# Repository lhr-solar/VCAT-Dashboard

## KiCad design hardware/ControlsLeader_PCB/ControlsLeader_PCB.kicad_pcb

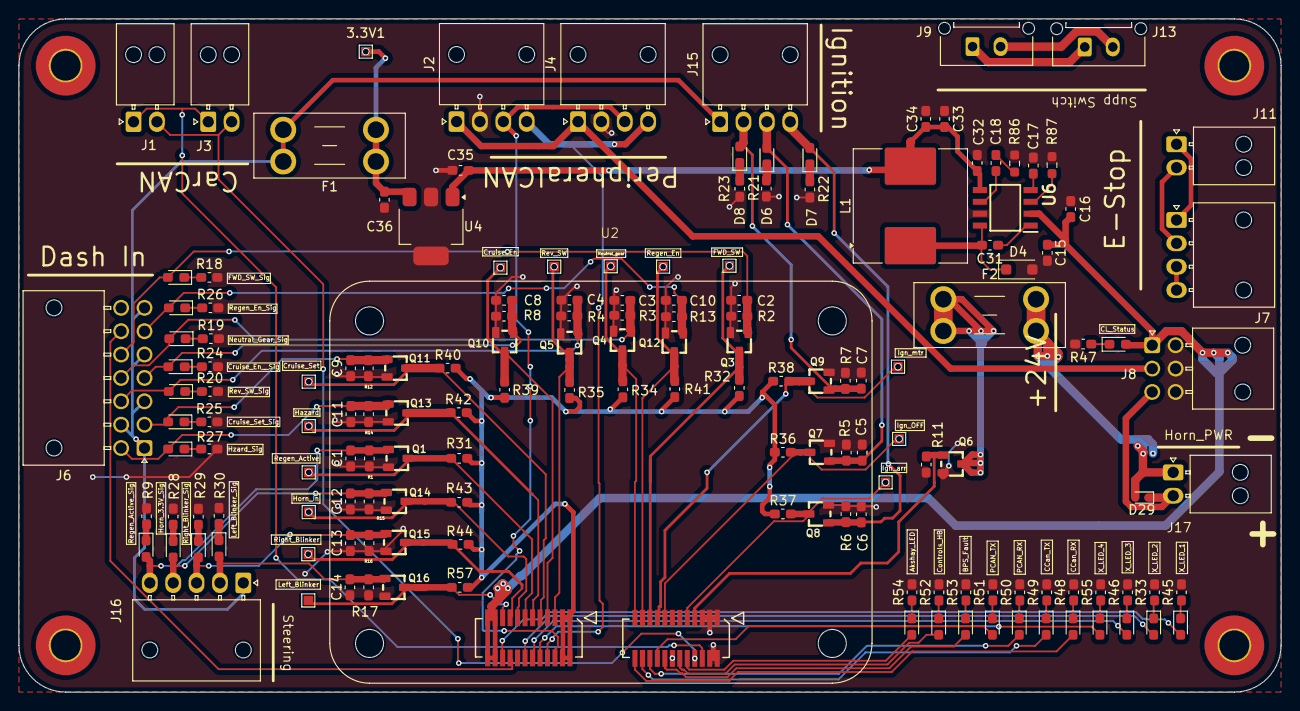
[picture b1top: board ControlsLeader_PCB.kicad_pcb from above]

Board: 2 copper layers, 135.0 x 72.0 mm, 162 parts (0 on the bottom side), 92 nets.

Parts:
3.3V1: TestPoint; TestPoint_Pad_1.0x1.0mm
C1, C2, C3, C4, C5, C6, C7, C8, C9, C10, C11, C12, C13, C14: 5uF; C_0603_1608Metric_Pad1.08x0.95mm_HandSolder
C15, C32, C33, C34, C35, C36: 10uF; C_0603_1608Metric_Pad1.08x0.95mm_HandSolder
C16: 1uF; C_0603_1608Metric_Pad1.08x0.95mm_HandSolder
C17: 10nF; C_0603_1608Metric_Pad1.08x0.95mm_HandSolder
C18: 3.3nF; C_0603_1608Metric_Pad1.08x0.95mm_HandSolder
C31: 0.1uF; C_0603_1608Metric_Pad1.08x0.95mm_HandSolder
Cruise_En: TestPoint; TestPoint_Pad_1.0x1.0mm
Cruise_En__Sig: GPIO_Status_Blue; LED_0603_1608Metric_Pad1.05x0.95mm_HandSolder
Cruise_Set: TestPoint; TestPoint_Pad_1.0x1.0mm
Cruise_Set_Sig: GPIO_Status_Blue; LED_0603_1608Metric_Pad1.05x0.95mm_HandSolder
D4: MBR230S1F; D_SOD-123F
D6, D7, D8: GPIO_Status_Blue; LED_0603_1608Metric_Pad1.05x0.95mm_HandSolder
D16: Controls_Leader_Status_Red; LED_0603_1608Metric_Pad1.05x0.95mm_HandSolder
D17, D18, D19, D20, D21, D22, D23, D24, D25, D26, D27: 0603_SMD; LED_0603_1608Metric_Pad1.05x0.95mm_HandSolder
D29: VSSAF522-M3/H; D_SOD-523
F1, F2: Fuse; Fuseholder_Blade_Mini_Keystone_3568
FWD_SW: TestPoint; TestPoint_Pad_1.0x1.0mm
FWD_SW_Sig: GPIO_Status_Blue; LED_0603_1608Metric_Pad1.05x0.95mm_HandSolder
H1, H2, H3, H4: M.3; MountingHole_3.2mm_M3_Pad_TopBottom
Hazard: TestPoint; TestPoint_Pad_1.0x1.0mm
Horn_3.3V_Sig: GPIO_Status_Blue; LED_0603_1608Metric_Pad1.05x0.95mm_HandSolder
Horn_In: TestPoint; TestPoint_Pad_1.0x1.0mm
Hzard_Sig: GPIO_Status_Blue; LED_0603_1608Metric_Pad1.05x0.95mm_HandSolder
Ign_OFF: TestPoint; TestPoint_Pad_1.0x1.0mm
Ign_arr: TestPoint; TestPoint_Pad_1.0x1.0mm
Ign_mtr: TestPoint; TestPoint_Pad_1.0x1.0mm
J1: CarCANConnector_Out; Molex_Nano-Fit_105313-xx02_1x02_P2.50mm_Horizontal
J2: PeripheralCAN_out; Molex_Nano-Fit_105313-xx04_1x04_P2.50mm_Horizontal
J3: CarCANConnector_In; Molex_Nano-Fit_105313-xx02_1x02_P2.50mm_Horizontal
J4: PeripheralCAN_in; Molex_Nano-Fit_105313-xx04_1x04_P2.50mm_Horizontal
J6: Conn_2Rows-13Pins; Molex_Nano-Fit_105314-xx14_2x07_P2.50mm_Horizontal
J7: Conn_01x04; Molex_Nano-Fit_105313-xx04_1x04_P2.50mm_Horizontal
J8: Dash_Lsom_Horn_Lights_PWR; Molex_Nano-Fit_105314-xx06_2x03_P2.50mm_Horizontal
J9: Supp_In; Molex_Micro-Fit_3.0_43650-0215_1x02_P3.00mm_Vertical
J11: EStop1; Molex_Nano-Fit_105313-xx02_1x02_P2.50mm_Horizontal
J13: Supp_Out; Molex_Micro-Fit_3.0_43650-0215_1x02_P3.00mm_Vertical
J15: IgnConn_01x04; Molex_Nano-Fit_105313-xx04_1x04_P2.50mm_Horizontal
J16: SteeringConn_01x05; Molex_Nano-Fit_105313-xx05_1x05_P2.50mm_Horizontal
J17: Conn_01x02; Molex_Nano-Fit_105313-xx02_1x02_P2.50mm_Horizontal
L1: 100uH; L_Coilcraft_MSS1246-XXX
Left_Blinker: TestPoint; TestPoint_Pad_1.0x1.0mm
Left_Blinker_Sig: GPIO_Status_Blue; LED_0603_1608Metric_Pad1.05x0.95mm_HandSolder
Neutral_Gear_Sig: GPIO_Status_Blue; LED_0603_1608Metric_Pad1.05x0.95mm_HandSolder
Neutral_gear: TestPoint; TestPoint_Pad_1.0x1.0mm
Q1, Q3, Q4, Q5, Q6, Q7, Q8, Q9, Q10, Q11, Q12, Q13, Q14, Q15, Q16: NMOS; SOT23
R1, R2, R3, R4, R5, R6, R7, R8, R11, R12, R13, R14, R15, R16, R17: 10k; C_0603_1608Metric_Pad1.08x0.95mm_HandSolder
R9, R18, R19, R20, R21, R22, R23, R24, R25, R26, R27, R28, R29, R30: 150; C_0603_1608Metric_Pad1.08x0.95mm_HandSolder
R31, R32, R34, R35, R36, R37, R38, R39, R40, R41, R42, R43, R44, R57: 100k; C_0603_1608Metric_Pad1.08x0.95mm_HandSolder
R33, R45, R46, R55: 65; C_0603_1608Metric_Pad1.08x0.95mm_HandSolder
R47: 1.1k; C_0603_1608Metric_Pad1.08x0.95mm_HandSolder
R48, R49, R50, R51, R52, R53, R54: 20; C_0603_1608Metric_Pad1.08x0.95mm_HandSolder
R86: 16k; R_0603_1608Metric_Pad0.98x0.95mm_HandSolder
R87: ROSC; R_0603_1608Metric_Pad0.98x0.95mm_HandSolder
Regen_Active: TestPoint; TestPoint_Pad_1.0x1.0mm
Regen_Active_Sig: GPIO_Status_Blue; LED_0603_1608Metric_Pad1.05x0.95mm_HandSolder
Regen_En: TestPoint; TestPoint_Pad_1.0x1.0mm
Regen_En_Sig: GPIO_Status_Blue; LED_0603_1608Metric_Pad1.05x0.95mm_HandSolder
Rev_SW: TestPoint; TestPoint_Pad_1.0x1.0mm
Rev_SW_Sig: GPIO_Status_Blue; LED_0603_1608Metric_Pad1.05x0.95mm_HandSolder
Right_Blinker: TestPoint; TestPoint_Pad_1.0x1.0mm
Right_Blinker_Sig: GPIO_Status_Blue; LED_0603_1608Metric_Pad1.05x0.95mm_HandSolder
U2: LeaderSOM
U4: LT1963AEST-3.3#TRPBF; SOT-223-3_TabPin2
U6: TPS5405DR

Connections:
+24V: C15.1, C16.1, D16.2 (A), J8.1, U2.21 (24VExt), U2.22 (24VExt), U2.23 (24VExt), U2.24 (24VExt), U6.2 (VIN)
/3.3V_LDO: F1.2, J6.1, J6.3, J6.5, J6.7, J6.9, J15.1, J16.1
/3.3V_LSOM: R31.1, R32.1, R34.1, R35.1, R36.1, R37.1, R38.1, R39.1, R40.1, R41.1, R42.1, R43.1, R44.1, R57.1, U2.1 (+3.3V), U2.2 (+3.3V), U2.3 (+3.3V), U2.4 (+3.3V)
/5V_LDO: C32.1, C33.1, C34.1, C35.1, L1.2, U4.1 (IN), U6.5 (VSENSE)
/5v_3.3v_LDO/3.3V_LDO: 3.3V1.1, C36.1, F1.1, U4.3 (OUT)
/24v_5v_Buck/ROSC: R87.1, U6.3 (ROSC)
/+24v_Horn: D29.1 (K), J8.3, J17.2
/+24v_Lights: J2.1 (24V), J4.1 (24V), J8.2
/Akshay_LED: D25.2 (A), U2.34 (UART4_TX)
/BPS_Fault_LED: D24.2 (A), U2.40 (ADC1_IN7)
/CarCan_H: J1.1 (CAN_H), J3.1 (CAN_H), U2.30 (CarCAN_H)
/CarCan_L: J1.2 (CAN_L), J3.2 (CAN_L), U2.32 (CarCAN_L)
/CarCan_RX_LED: D19.2 (A), U2.48 (SPI3_SCK)
/CarCan_TX_LED: D20.2 (A), U2.46 (SPI3_MOSI)
/Controls_HB_LED: D23.2 (A), U2.36 (UART4_RX)
/Cruise_Enable_GPIO_IN: Cruise_En.1, Q10.1 (D), R39.2, U2.7 (I2C4_SCL)
/Cruise_Enable_Signal: C8.2, Cruise_En__Sig.2 (A), J6.4, Q10.2 (G), R8.2
/Cruise_Set_GPIO_IN: Cruise_Set.1, Q11.1 (D), R40.2, U2.9 (I2C3_SDA)
/Cruise_Set_Signal: C9.2, Cruise_Set_Sig.2 (A), J6.2, Q11.2 (G), R12.2
/Dash/Contactor_IN1: J7.2, J11.2
/Dash/Contactor_OUT1: J7.1, J11.1
/Dash/Contactor_OUT2: J7.3, J7.4
/Dash/LV-: J9.2, J13.2
/Dash/LV_EN: J9.1, J13.1
/Extra_LED1: D17.2 (A), U2.20 (SPI2_SCK)
/Extra_LED2: D18.2 (A), U2.14 (SPI2_MISO)
/Extra_LED3: D26.2 (A), U2.12 (ADC1_IN11)
/Extra_LED4: D27.2 (A), U2.10 (ADC2_IN12)
/Fwd_SW_GPIO: FWD_SW.1, Q3.1 (D), R32.2, U2.43 (ADC1_IN1)
/Fwd_SW_Signal: C2.2, FWD_SW_Sig.2 (A), J6.12, Q3.2 (G), R2.2
/Hazard_GPIO_IN: Hazard.1, Q13.1 (D), R42.2, U2.11 (I2C3_SCL)
/Hazard_Signal: C11.2, Hzard_Sig.2 (A), J6.8, Q13.2 (G), R14.2
/Horn_3.3V_Signal: C12.2, Horn_3.3V_Sig.2 (A), J16.4, Q14.2 (G), R15.2
/Horn_24V_Signal_Out: D29.2 (A), F2.2, J17.1
/Horn_GPIO_IN: Horn_In.1, Q14.1 (D), R43.2, U2.15 (UART5_RX)
/Horn_GPIO_OUT: Q6.2 (G), R11.1, U2.31 (ADC1_IN12)
/Ign_OFF_GPIO: Ign_OFF.1, Q7.1 (D), R36.2, U2.39 (ADC1_IN3)
/Ign_arr_GPIO: Ign_arr.1, Q8.1 (D), R37.2, U2.33 (ADC1_IN15)
/Ign_arr_Signal: C6.2, D7.2 (A), J15.4, Q8.2 (G), R6.2
/Ign_mtr_GPIO: Ign_mtr.1, Q9.1 (D), R38.2, U2.41 (ADC1_IN2)
/Ign_mtr_Signal: C7.2, D8.2 (A), J15.2, Q9.2 (G), R7.2
/Ign_off_Signal: C5.2, D6.2 (A), J15.3, Q7.2 (G), R5.2
/Indicator_PWM: J6.13, U2.18 (SPI2_MOSI)
/Left_Blinker_ON: Left_Blinker.1, Q16.1 (D), R57.2, U2.19 (USART1_RX)
/Left_Blinker_Signal: C14.2, J16.2, Left_Blinker_Sig.2 (A), Q16.2 (G), R17.2
/Neutral_Gear_GPIO: Neutral_gear.1, Q4.1 (D), R34.2, U2.47 (ADC1_IN6)
/Neutral_Gear_Signal: C3.2, J6.11, Neutral_Gear_Sig.2 (A), Q4.2 (G), R3.2
/PH_Can_RX_LED: D21.2 (A), U2.44 (SPI3_NSS)
/PH_Can_TX_LED: D22.2 (A), U2.42 (SPI3_MISO)
/PerCan_H: J2.3 (CAN_H), J4.3 (CAN_H), U2.6 (IntCAN_H)
/PerCan_L: J2.4 (CAN_L), J4.4 (CAN_L), U2.8 (IntCAN_L)
/Regen_Active_GPIO_IN: Q1.1 (D), R31.2, Regen_Active.1, U2.13 (UART5_TX)
/Regen_Active_Signal: C1.2, J16.5, Q1.2 (G), R1.2, Regen_Active_Sig.2 (A)
/Regen_Enable_GPIO_IN: Q12.1 (D), R41.2, Regen_En.1, U2.45 (ADC1_IN8)
/Regen_Enable_Signal: C10.2, J6.6, Q12.2 (G), R13.2, Regen_En_Sig.2 (A)
/Rev_SW_GPIO: Q5.1 (D), R35.2, Rev_SW.1, U2.5 (I2C4_SDA)
/Rev_SW_Signal: C4.2, J6.10, Q5.2 (G), R4.2, Rev_SW_Sig.2 (A)
/Right_Blinker_ON: Q15.1 (D), R44.2, Right_Blinker.1, U2.17 (USART1_TX)
/Right_Blinker_Signal: C13.2, J16.3, Q15.2 (G), R16.2, Right_Blinker_Sig.2 (A)
GND: C1.1, C2.1, C3.1, C4.1, C5.1, C6.1, C7.1, C8.1, C9.1, C10.1, C11.1, C12.1, C13.1, C14.1, C15.2, C16.2, C17.2, C32.2, C33.2, C34.2, C35.2, C36.2, D4.2 (A), J2.2 (GND), J4.2 (GND), J8.4, J8.5, J8.6, Q1.3 (S), Q3.3 (S), Q4.3 (S), Q5.3 (S), Q6.3 (S), Q7.3 (S), Q8.3 (S), Q9.3 (S), Q10.3 (S), Q11.3 (S), Q12.3 (S), Q13.3 (S), Q14.3 (S), Q15.3 (S), Q16.3 (S), R1.1, R2.1, R3.1, R4.1, R5.1, R6.1, R7.1, R8.1, R9.2, R11.2, R12.1, R13.1, R14.1, R15.1, R16.1, R17.1, R18.2, R19.2, R20.2, R21.2, R22.2, R23.2, R24.2, R25.2, R26.2, R27.2, R28.2, R29.2, R30.2, R33.2, R45.2, R46.2, R47.2, R48.2, R49.2, R50.2, R51.2, R52.2, R53.2, R54.2, R55.2, R86.2, R87.2, U2.25 (GND), U2.26 (GND), U2.27 (GND), U2.28 (GND), U2.29 (GND), U2.38 (GNDA), U4.2 (GND), U6.7 (GND)
unnamed: C18.2, R86.1
unnamed: R9.1, Regen_Active_Sig.1 (K)
unnamed: FWD_SW_Sig.1 (K), R18.1
unnamed: Neutral_Gear_Sig.1 (K), R19.1
unnamed: C31.2, D4.1 (K), L1.1, U6.8 (LX)
unnamed: R20.1, Rev_SW_Sig.1 (K)
unnamed: D6.1 (K), R21.1
unnamed: D7.1 (K), R22.1
unnamed: D8.1 (K), R23.1
unnamed: Cruise_En__Sig.1 (K), R24.1
unnamed: Cruise_Set_Sig.1 (K), R25.1
unnamed: R26.1, Regen_En_Sig.1 (K)
unnamed: Hzard_Sig.1 (K), R27.1
unnamed: Horn_3.3V_Sig.1 (K), R28.1
unnamed: R29.1, Right_Blinker_Sig.1 (K)
unnamed: Left_Blinker_Sig.1 (K), R30.1
unnamed: D16.1 (K), R47.1
unnamed: D17.1 (K), R45.1
unnamed: D18.1 (K), R33.1
unnamed: D19.1 (K), R48.1
unnamed: D20.1 (K), R49.1
unnamed: D21.1 (K), R50.1
unnamed: D22.1 (K), R51.1
unnamed: D23.1 (K), R52.1
unnamed: D24.1 (K), R53.1
unnamed: D25.1 (K), R54.1
unnamed: D26.1 (K), R46.1
unnamed: D27.1 (K), R55.1
unnamed: F2.1, Q6.1 (D)
unnamed: C31.1, U6.1 (BOOT)
unnamed: C18.1, U6.6 (COMP)
unnamed: C17.1, U6.4 (SS)

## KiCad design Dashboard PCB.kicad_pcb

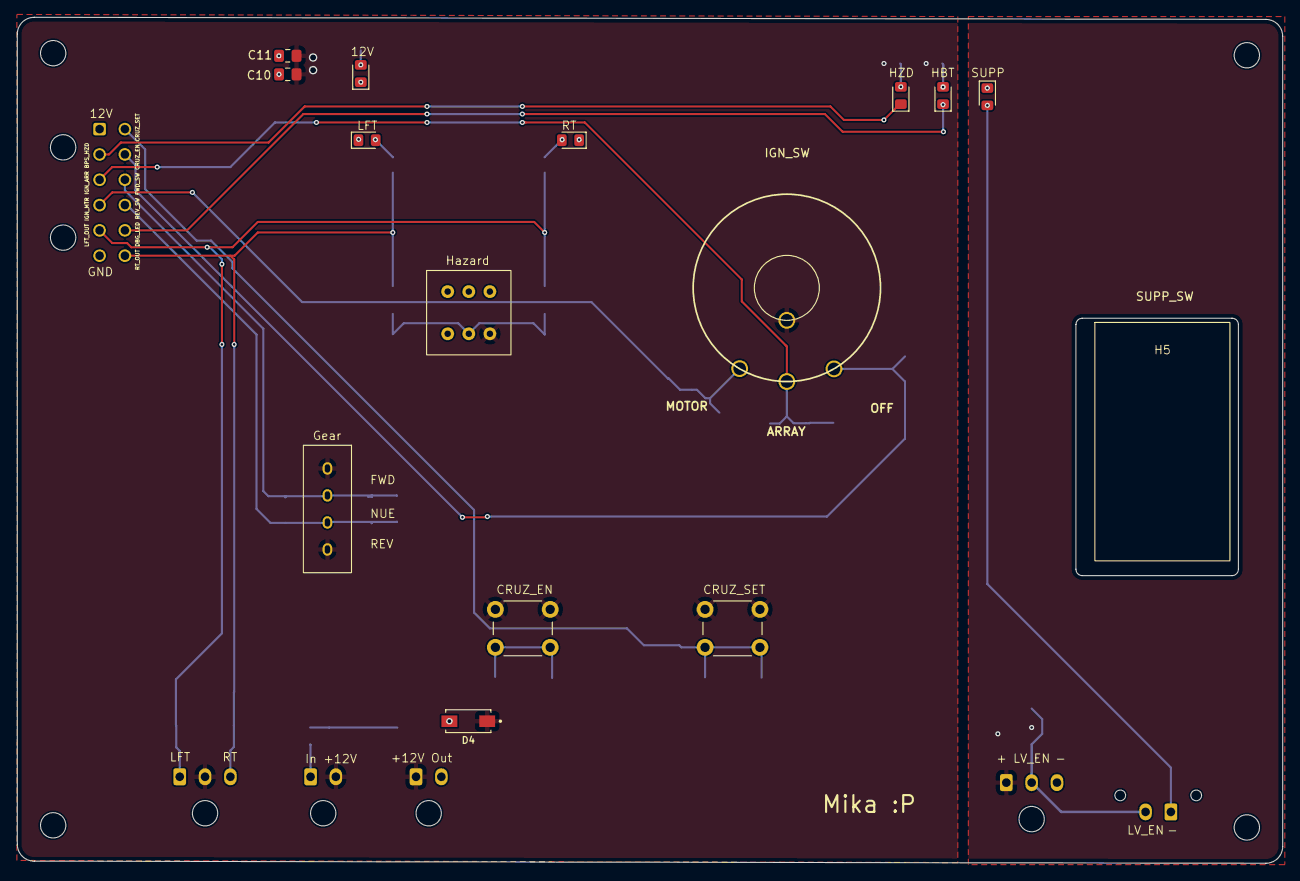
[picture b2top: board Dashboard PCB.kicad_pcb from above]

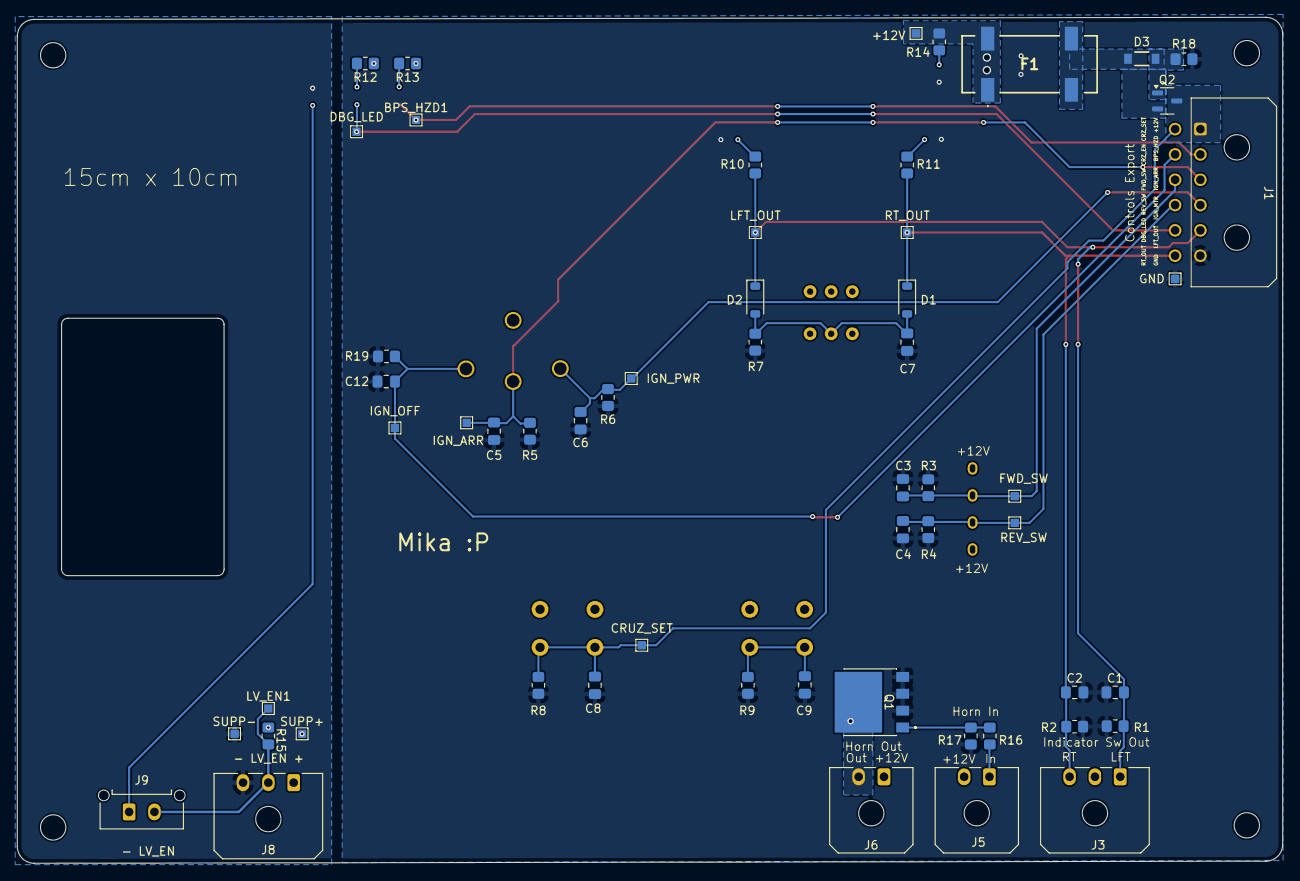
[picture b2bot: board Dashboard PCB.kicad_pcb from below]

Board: 2 copper layers, 150.0 x 100.2 mm, 75 parts (56 on the bottom side), 28 nets.

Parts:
12V_PWR1: SMD_0805; LED_0805_2012Metric_Pad1.15x1.40mm_HandSolder
+12V: TestPoint; TestPoint_Pad_1.0x1.0mm
BPS_HZD1: TestPoint; TestPoint_Pad_1.0x1.0mm
BPS_HZD_LED1: SMD_0805_RED; LED_0805_2012Metric_Pad1.15x1.40mm_HandSolder
C1, C2, C3, C4, C5, C6, C7, C8, C9, C12: 5uF; C_0805_2012Metric_Pad1.18x1.45mm_HandSolder
C10, C11: 100uF; C_0805_2012Metric_Pad1.18x1.45mm_HandSolder
CRUZ_EN_SW1: CRUSE_EN_SW_12V; SW_PUSH_6mm
CRUZ_SET: TestPoint; TestPoint_Pad_1.0x1.0mm
CRUZ_SET_SW1: CRUSE_SET_SW_12V; SW_PUSH_6mm
D1, D2: BAV16W; D_SOD-123
D3: BZT52-B12-QX; BZT52B12QX
D4: VSSAF522; DO-221AC
DBG_LED: TestPoint; TestPoint_Pad_1.0x1.0mm
F1: Fuse; 3588
FWD_SW: TestPoint; TestPoint_Pad_1.0x1.0mm
GEAR_SW_12V1: GR_SW1; 3posSlideToggle
GND: TestPoint; TestPoint_Pad_1.0x1.0mm
H1, H2, H3, H4: MountingHole; MountingHole_3mm
H5: SuppSwitchMount; Supp_Switch
HZD_SW1: HAZARD_SWITCH_12V; Toggle
Heartbeat_LED1: SMD_0805_GRN; LED_0805_2012Metric_Pad1.15x1.40mm_HandSolder
IGN_ARR: TestPoint; TestPoint_Pad_1.0x1.0mm
IGN_OFF: TestPoint; TestPoint_Pad_1.0x1.0mm
IGN_PWR: TestPoint; TestPoint_Pad_1.0x1.0mm
IGN_SW1: IGNITION_SW_12V; SW_3POS_ROT
J1: Controls_Leader_Export_02x06; Molex_Micro-Fit_3.0_43045-1200_2x06_P3.00mm_Horizontal
J3: INDICATOR_SWITCH_OUT; Molex_Micro-Fit_3.0_43650-0300_1x03_P3.00mm_Horizontal
J5: Horn_In_01x02; Molex_Micro-Fit_3.0_43650-0200_1x02_P3.00mm_Horizontal
J6: Horn_Out_01x02; Molex_Micro-Fit_3.0_43650-0200_1x02_P3.00mm_Horizontal
J8: Supp_Out; Molex_Micro-Fit_3.0_43650-0300_1x03_P3.00mm_Horizontal
J9: Supp_In; Molex_Micro-Fit_3.0_43650-0215_1x02_P3.00mm_Vertical
LFT_LED1: SMD_0805; LED_0805_2012Metric_Pad1.15x1.40mm_HandSolder
LFT_OUT: TestPoint; TestPoint_Pad_1.0x1.0mm
LV_EN1: TestPoint; TestPoint_Pad_1.0x1.0mm
Q1: TO200P800X182-5N
Q2: Q_PMOS_GDS; SOT-23-3
R1, R2, R3, R4, R5, R6, R7, R8, R9, R17, R19: 10k; R_0805_2012Metric_Pad1.20x1.40mm_HandSolder
R10, R11, R12, R13, R14, R15: 5.1k; R_0805_2012Metric_Pad1.20x1.40mm_HandSolder
R16: 1k; R_0805_2012Metric_Pad1.20x1.40mm_HandSolder
R18: 100k; R_0805_2012Metric_Pad1.20x1.40mm_HandSolder
REV_SW: TestPoint; TestPoint_Pad_1.0x1.0mm
RT_LED1: SMD_0805; LED_0805_2012Metric_Pad1.15x1.40mm_HandSolder
RT_OUT: TestPoint; TestPoint_Pad_1.0x1.0mm
SUPP1: LED; LED_0805_2012Metric_Pad1.15x1.40mm_HandSolder
SUPP+: TestPoint; TestPoint_Pad_1.0x1.0mm
SUPP-: TestPoint; TestPoint_Pad_1.0x1.0mm

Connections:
+12V: +12V.1, C10.1, C11.1, CRUZ_EN_SW1.1, CRUZ_SET_SW1.1, D4.C (K), F1.1, GEAR_SW_12V1.1, GEAR_SW_12V1.4, HZD_SW1.1, IGN_SW1.1, J3.2, J5.2, J6.1, R12.1, R13.1, R14.1
/BPS_HZD: BPS_HZD1.1, BPS_HZD_LED1.1 (K), J1.2
/CRUZ_EN: C12.1, IGN_OFF.1, IGN_SW1.4, J1.8, R19.2
/CRUZ_SET: C8.1, CRUZ_SET.1, CRUZ_SET_SW1.2, J1.7, R8.1
/DBG_LED: DBG_LED.1, Heartbeat_LED1.1 (K), J1.11
/FWD_SW: C3.2, FWD_SW.1, GEAR_SW_12V1.2, J1.9, R3.2
/IGN_ARR: C5.1, IGN_ARR.1, IGN_SW1.3, J1.3, R5.2
/IGN_MTR: C6.1, IGN_PWR.1, IGN_SW1.2, J1.4, R6.2
/LFT_OUT: C1.2, D2.1 (K), J1.5, J3.1, LFT_OUT.1, R1.1, R10.1
/LV_EN: J8.2, J9.2, LV_EN1.1, R15.2
/Led: J9.1, SUPP1.2 (A)
/PWR: J1.1, Q2.3 (S)
/REV_SW: C4.1, GEAR_SW_12V1.3, J1.10, R4.1, REV_SW.1
/RT_OUT: C2.1, D1.1 (K), J1.12, J3.3, R2.2, R11.1, RT_OUT.1
/Supp+: J8.1, R15.1, SUPP+.1
/Supp-: J8.3, SUPP1.1 (K), SUPP-.1
GND: 12V_PWR1.1 (K), C1.1, C2.2, C3.1, C4.2, C5.2, C6.2, C7.2, C8.2, C9.2, C10.2, C11.2, C12.2, GND.1, J1.6, LFT_LED1.1 (K), Q1.3 (S), R1.2, R2.1, R3.1, R4.2, R5.1, R6.1, R7.1, R8.2, R9.1, R17.2, R18.1, R19.1, RT_LED1.1 (K)
unnamed: 12V_PWR1.2 (A), R14.2
unnamed: BPS_HZD_LED1.2 (A), R13.2
unnamed: C7.1, D1.2 (A), D2.2 (A), HZD_SW1.2, R7.2
unnamed: D3.2 (A), Q2.1 (G), R18.2
unnamed: D3.1 (K), F1.2, Q2.2 (D)
unnamed: Heartbeat_LED1.2 (A), R12.2
unnamed: J5.1, R16.2
unnamed: D4.A, J6.2, Q1.1 (D)
unnamed: LFT_LED1.2 (A), R10.2
unnamed: Q1.2 (G), R16.1, R17.1
unnamed: R11.2, RT_LED1.2 (A)

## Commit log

2025-04-05 fixed
2025-04-09 Johnathan
    Added FET for horn, fixed other stuff, etc
2025-04-09 pea left pant
2025-04-09 franK
2025-04-09 Nuked some thigns
2025-04-12 Quick change (fuse not added yet)
2025-04-13 ravi and lakshay are so mean to me
2025-04-13 stuff
2025-04-16 removed old files
2025-04-16 added stuff
2025-05-17 added flyback and made supp hole bigger
2025-05-17 hole
2025-05-26 make ign off cruz en or some shit
2025-10-04 Branch Init
2025-10-11 Schematic done, GPIO on .ioc TBD
2025-10-11 Board review
2025-10-11 Fixing kicad sharepoint
2025-10-11 Reinit KiCAD Sharepoint
2025-10-11 Schematic Backup
2025-10-11 DONE!!! - just need to add footprints + part #s)
2025-10-12 now DONE!!! - still needs footprints
2025-10-12 Schematic Ready for Review - Just need FET footprints to be confirmed
2025-10-12 LDO Subpage renamed - still need FET footprints
2025-10-13 Ready for final review
2025-10-14 Removed Extra LED 6
2025-10-14 Updated LSOM status LED and horn 24v signal connector layout
2025-10-14 All footprints added
2025-10-14 Schematic RevA
2025-10-16 PCB DESIGN DONE - need to add datasheets and p/n
2025-10-17 Updated GPIO table, addressed lakshay review
2025-10-17 3D Models, Logos, Lakshay Reviews #2 done
2025-10-17 Added RevA Text
2025-10-18 Addressed Lakshay's Review 3
2025-10-18 Updated 5v_ldo fill zone
2025-10-19 Final reviews addressed - RevA
2025-10-19 Fixed DRC errors, and indicator switch pwr/pwm output conn to steering
2025-10-25 BOM!
2025-10-25 BOMMMM
2025-11-22 Revision A (#4)
    * Branch Init
    * Schematic done, GPIO on .ioc TBD
    * Board review
    * Fixing kicad sharepoint
    * Reinit KiCAD Sharepoint
    * Schematic Backup
2025-11-22 Add README.md for Controls Leader documentation
    Added detailed documentation for the Controls Leader board, including hardware architecture, input interfaces, and repository structure.
